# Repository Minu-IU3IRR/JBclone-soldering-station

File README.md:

# DIY Multi-Channel JBC-Compatible Soldering Station

A high-performance open hardware soldering station designed to support **JBC and other thermocouple-based soldering tips**.  
This project aims to deliver professional-grade thermal control and user experience at a fraction of the cost of a commercial JBC system.

---

## Overview

The system provides **multi-channel support**, each with independent temperature feedback loops based on PID control.  
It includes modular PCB designs, 3D-printable case that fits in a standard 200x200mm 3d printer, STM32F103 microcontroller, Nextion HMI interface

**Key features:**
- Multi-channel indipendent temperature control
- Compatible with any arbitrary tip, JBC or otherwise, as long as it uses a thermocouple
- PID temperature control with zero cross switching
- external EEprom stored calcibration and tuning  
- Nextion-based HMI for user interaction
- Fully open-source hardware and firmware

---
## Firmware Architecture

The firmware is structured into modules:

| Module | Description |
|---------|-------------|
| **Heater/** | PID controller, temperature processing, and power control routines |
| **EEprom/** | Persistent storage for calibration and configuration |
| **Hardware_definition/** | Board pin mapping, timing constants, and I/O configuration |
| **display/** | Nextion display communication handler |
| **hartbeat/** | System heartbeat and status indicator |
| **Parser/** | Command parser for serial/HMI communication |

**PID Control:**  
The controller continuously adjusts heater drive based on thermocouple feedback.  
Parameters `Kp`, `Ki`, and `Kd` can be tuned at runtime through serial commands or tuning software.

**EEPROM Configuration:**  
All configuration data (tip profiles, PID tuning, calibration) is saved in EEPROM.  
On startup, the station loads the saved configuration automatically.

---

## Hardware Assembly

1. **PCBs:**  
   Fabricate the `mainboard` and `daughterboard` Gerbers (found under `/production/`).
2. **Mechanical design:**  
   View or download the CAD model on Onshape:  
   👉 [Onshape Assembly Model](https://cad.onshape.com/documents/a679f571d3dbe280f604253c/w/8a053e0b812f1b7821749418/e/78f31934af3d4bb4e1cbee4a)
3. **Transformer:**  
   Follow winding and connection details from the `transformer/` folder or pick a closely matched one (MUST HAVE INDIPENDENT WINDINGS FOR EACH OUTPUT)

---

## 🖥️ HMI Setup

1. Open `NX3224T024_hmi.HMI` in **Nextion Editor**.
2. Connect the display to the mainboard’s UART (`Serial1`, 115200 bps).
3. Upload the `.tft` file to the screen via SD card or serial upload or upload via SD-card, check Nextion documentation
5. The interface provides:
   - Channel selection  
   - Temperature setpoint entry  
   - Live tip temperature display

---

## Software Build

1. **Install [PlatformIO](https://platformio.org/).**
2. Open `Software/JBclone Firmware/` in VS Code.
3. Connect your STM32 board using an ST-link dongle.
4. Build and upload:
   ```bash
   pio run --target upload
   ```
5. The firmware will automatically initialize EEPROM and start monitoring the heater.

---

## Calibration & Tuning

- Refer to `cal and tuning table.ods` for measured offsets and recommended PID coefficients.  
- Store calibration through serial commands or via tuning software.  
- EEPROM ensures retention between power cycles.

---

## License

**Hardware (PCBs, transformer, mechanical design):**  
Released under the [CERN-OHL-P v2 License](https://ohwr.org/project/cernohl/wikis/Documents/CERN-OHL-version-2).  
You are free to use, modify, and distribute, provided attribution to the original project is maintained.  

**Firmware and software:**  
Released under the [MIT License](https://opensource.org/licenses/MIT).  

All content is provided **as-is** without any warranty or liability.  
Please include a reference to this repository when sharing or modifying the design.

---

## Credits

Project designed and developed by Manuel Minutello.  
Hardware and firmware are open for modification and improvement by the community.

---

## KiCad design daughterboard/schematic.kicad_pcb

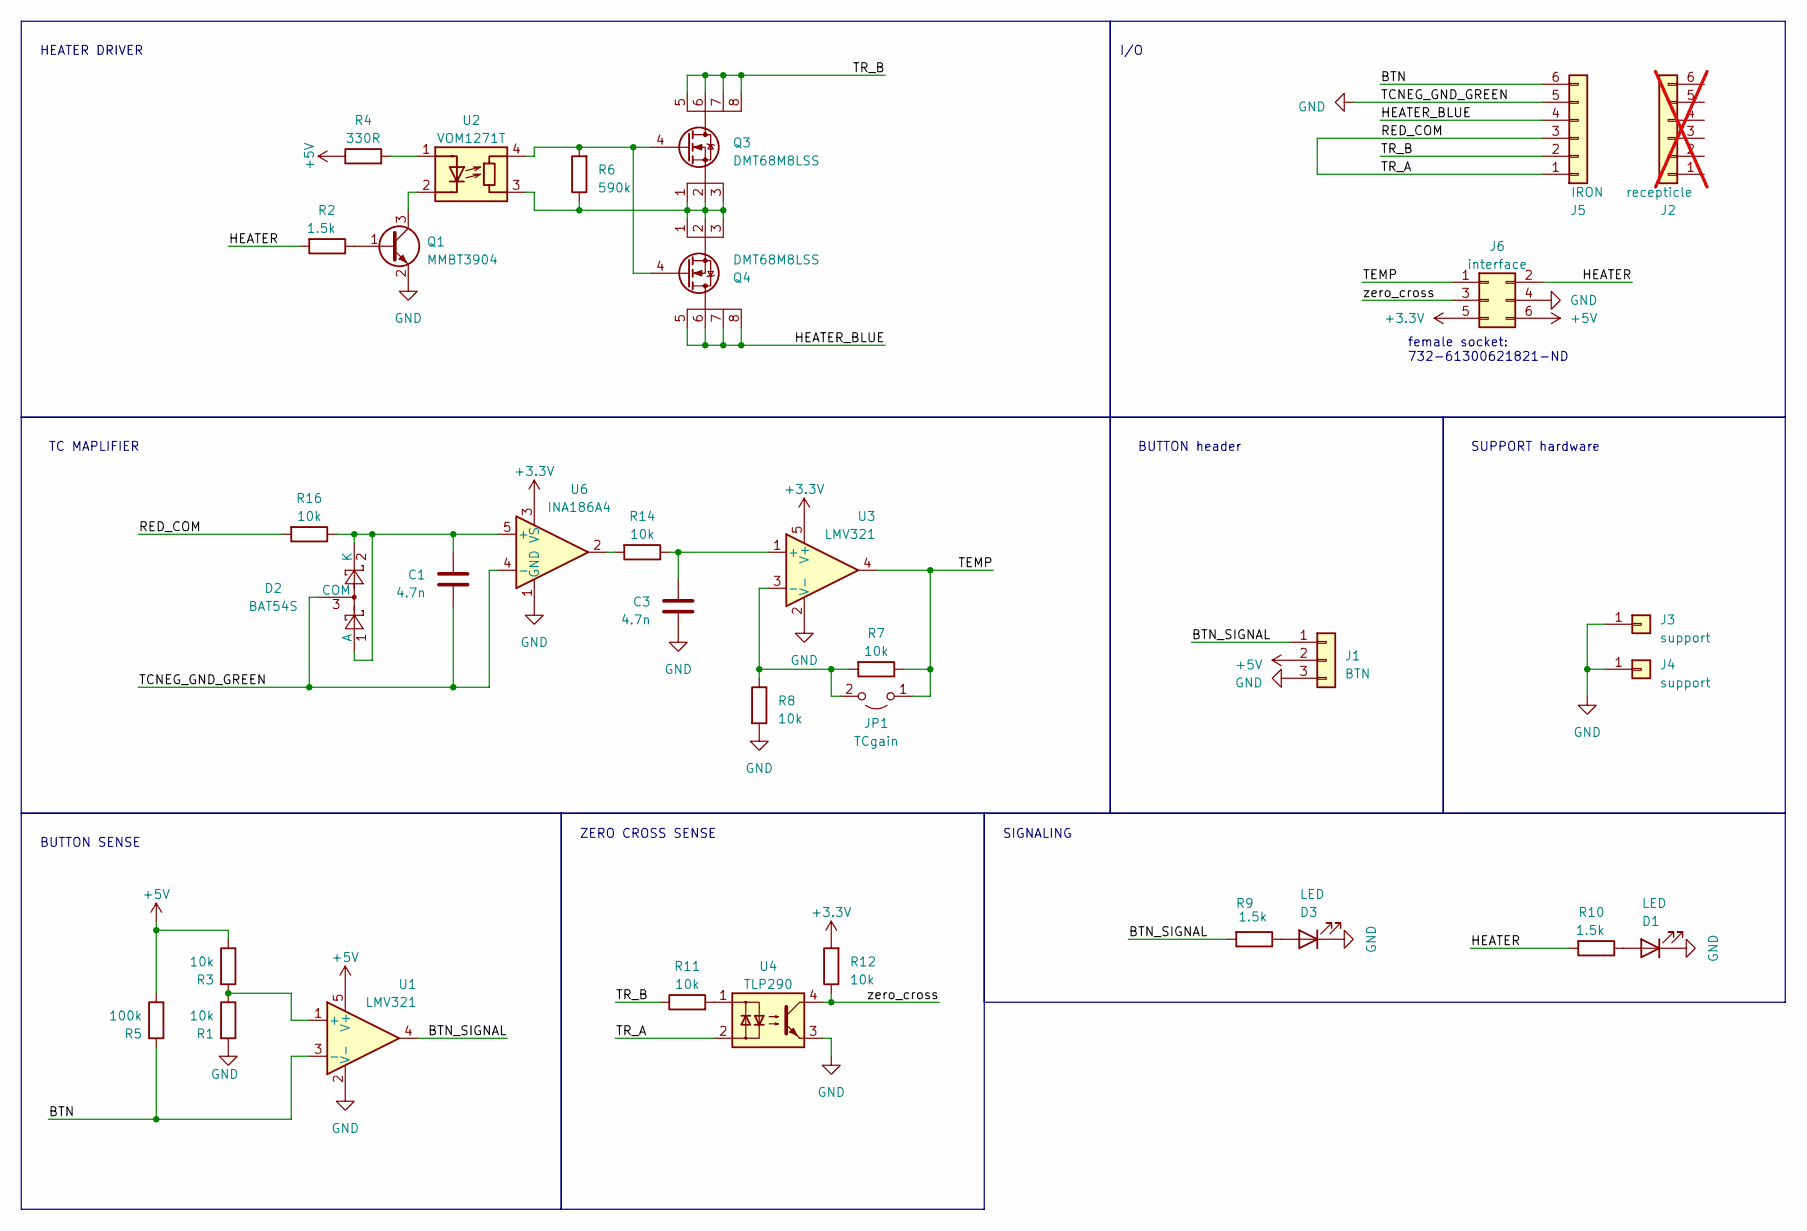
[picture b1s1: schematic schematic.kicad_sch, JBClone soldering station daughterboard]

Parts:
C1, C3: 4.7n; C_0805_2012Metric_Pad1.18x1.45mm_HandSolder; digikey 490-1634-1-ND
D1, D3: LED; LED_0805_2012Metric_Pad1.15x1.40mm_HandSolder; digikey 1516-QBLP631-IG5CT-ND
D2: BAT54S; SOT-23; digikey BAT54S-FDICT-ND
J1: BTN; PinHeader_1x03_P2.54mm_Vertical; digikey 10129378-903004BLF-ND
J2: recepticle; digikey 277-1015-ND; not fitted
J3, J4: support; AMT0440051DB; digikey 1818-AMT0440051DB0000G-ND
J5: IRON; PhoenixContact_MSTB_2,5_6-GF-5,08_1x06_P5.08mm_Horizontal_T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; digikey 277-1099-ND
J6: interface; PinHeader_2x03_P2.54mm_Horizontal; digikey 4324-PHED-RS006G1ABOGA-C006-ND
JP1: TCgain; SolderJumper-2_P1.3mm_Open_RoundedPad1.0x1.5mm; digikey NA
Q1: MMBT3904; SOT-23; digikey MMBT3904TPMSCT-ND
Q3, Q4: DMT68M8LSS; SO-8_3.9x4.9mm_P1.27mm; digikey 31-DMT68M8LSS-13CT-ND
R1, R3, R7, R8, R14, R16: 10k; R_0805_2012Metric_Pad1.20x1.40mm_HandSolder; digikey P10KACT-ND
R2, R9, R10: 1.5k; R_0805_2012Metric_Pad1.20x1.40mm_HandSolder; digikey 311-1.5KARCT-ND
R4: 330R; R_0805_2012Metric_Pad1.20x1.40mm_HandSolder; digikey P330ACT-ND
R5: 100k; R_0805_2012Metric_Pad1.20x1.40mm_HandSolder; digikey P100KACT-ND
R6: 590k; R_0805_2012Metric_Pad1.20x1.40mm_HandSolder; digikey P590KDACT-ND
R11, R12: 10k; R_0805_2012Metric; digikey P10KACT-ND
U1, U3: LMV321; SOT-23-5_HandSoldering; digikey 296-9567-1-ND
U2: VOM1271T; SOP-4; digikey VOM1271TCT-ND
U4: TLP290; SOP-4_4.4x2.6mm_P1.27mm; digikey TLP290(GB-TPSECT-ND
U6: INA186A4; SOT-23-5; digikey 296-INA186A4QDBVRQ1CT-ND

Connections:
+3.3V: J6.5, R12.2, U3.5 (V+), U6.3 (VS)
+5V: J1.2, J6.6, R3.1, R4.1, R5.1, U1.5 (V+)
/BTN: J5.6, R5.2, U1.3 (-)
/BTN_SIGNAL: J1.1, R9.2, U1.4
/HEATER: J6.2, R2.2, R10.2
/HEATER_BLUE: J5.4, Q4.5 (D), Q4.6 (D), Q4.7 (D), Q4.8 (D)
/RED_COM: J5.1, J5.3, R16.2, U4.2
/TEMP: J6.1, JP1.1 (A), R7.1, U3.4
/TR_B: J5.2, Q3.5 (D), Q3.6 (D), Q3.7 (D), Q3.8 (D), R11.1
/zero_cross: J6.3, R12.1, U4.4
GND: C1.2, C3.2, D1.1 (K), D2.3 (COM), D3.1 (K), J1.3, J3.1, J4.1, J5.5, J6.4, Q1.2 (E), R1.2, R8.2, U1.2 (V-), U3.2 (V-), U4.3, U6.1 (GND), U6.4 (-)
unnamed: D1.2 (A), R10.1
unnamed: C1.1, D2.1 (A), D2.2 (K), R16.1, U6.5 (+)
unnamed: D3.2 (A), R9.1
unnamed: JP1.2 (B), R7.2, R8.1, U3.3 (-)
unnamed: Q1.1 (B), R2.1
unnamed: Q1.3 (C), U2.2 (K)
unnamed: Q3.1 (D), Q3.2 (D), Q3.3 (G), Q4.1 (D), Q4.2 (D), Q4.3 (G), R6.1, U2.3 (R)
unnamed: Q3.4 (S), Q4.4 (S), R6.2, U2.4 (R)
unnamed: R11.2, U4.1
unnamed: R14.2, U6.2
unnamed: R1.1, R3.2, U1.1 (+)
unnamed: R4.2, U2.1 (A)
unnamed: C3.1, R14.1, U3.1 (+)

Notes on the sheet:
HEATER DRIVER
SIGNALING
female socket: 732-61300621821-ND
I/O
SUPPORT hardware
TC MAPLIFIER
BUTTON SENSE
ZERO CROSS SENSE
BUTTON header

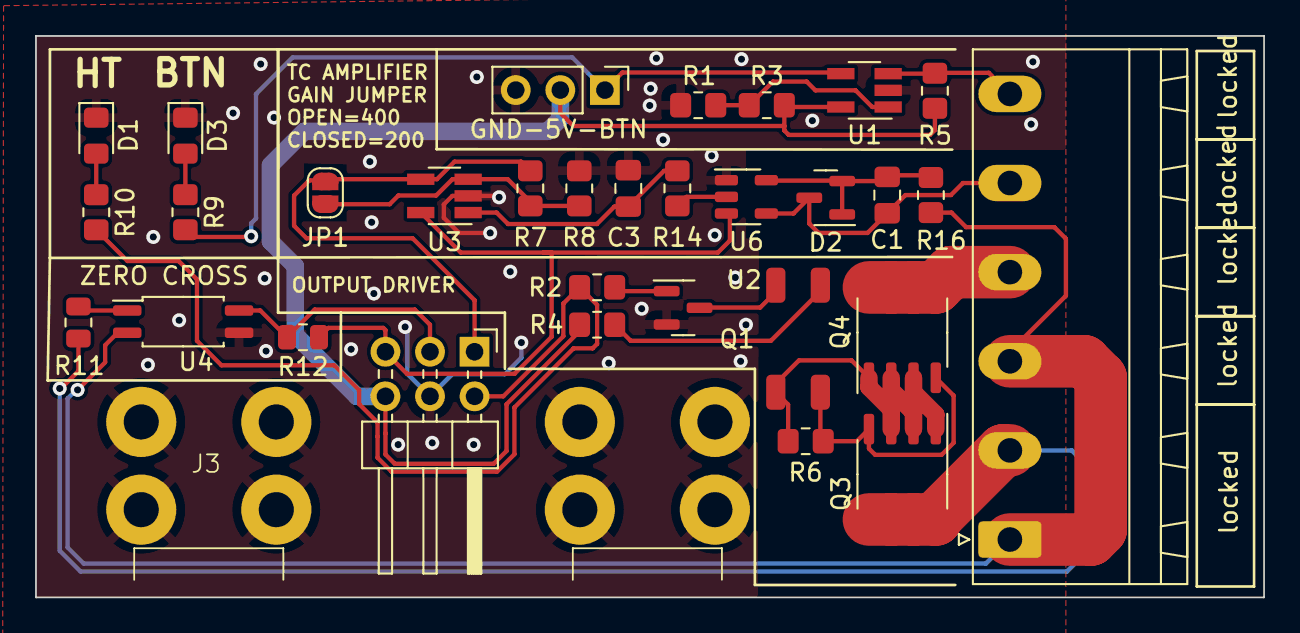
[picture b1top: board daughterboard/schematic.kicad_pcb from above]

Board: 2 copper layers, 70.0 x 32.0 mm, 33 parts (0 on the bottom side), 24 nets.

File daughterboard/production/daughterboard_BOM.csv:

"Reference","Value","Footprint","Datasheet","digikey","Qty"
"C1, C3","4.7n","Capacitor_SMD:C_0805_2012Metric_Pad1.18x1.45mm_HandSolder","https://search.murata.co.jp/Ceramy/image/img/A01X/G101/ENG/G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","490-1634-1-ND","2"
"D1, D3","LED","LED_SMD:LED_0805_2012Metric_Pad1.15x1.40mm_HandSolder","https://www.qt-brightek.com/datasheet/QBLP631-IG5.pdf","1516-QBLP631-IG5CT-ND","2"
"D2","BAT54S","Package_TO_SOT_SMD:SOT-23","https://www.diodes.com/assets/Datasheets/BAT54_A_C_S.pdf","BAT54S-FDICT-ND","1"
"J1","BTN","Connector_PinHeader_2.54mm:PinHeader_1x03_P2.54mm_Vertical","https://cdn.amphenol-cs.com/media/wysiwyg/files/documentatio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","10129378-903004BLF-ND","1"
"J2","recepticle","","https://www.phoenixcontact.com/en-us/products/pcb-plug-mstb-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","277-1015-ND","1"
"J3, J4","support","01_custom footprint:AMT0440051DB","https://www.anytek.com.cn/Upload/AMT0440051DB0000G-67c577521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","1818-AMT0440051DB0000G-ND","2"
"J5","IRON","Connector_Phoenix_MSTB:PhoenixContact_MSTB_2,5_6-GF-5,08_1x06_P5.08mm_Horizontal_ThreadedFlange","https://www.phoenixcontact.com/us/products/1759059/pdf","277-1099-ND","1"
"J6","interface","Connector_PinHeader_2.54mm:PinHeader_2x03_P2.54mm_Horizontal","https://mm.digikey.com/Volume0/opasdata/d220001/medias/docus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","4324-PHED-RS006G1ABOGA-C006-ND","1"
"JP1","TCgain","Jumper:SolderJumper-2_P1.3mm_Open_RoundedPad1.0x1.5mm","NA","NA","1"
"Q1","MMBT3904","Package_TO_SOT_SMD:SOT-23","https://www.mccsemi.com/pdf/Products/MMBT3904(SOT-23).pdf","MMBT3904TPMSCT-ND","1"
"Q3, Q4","DMT68M8LSS","Package_SO:SO-8_3.9x4.9mm_P1.27mm","https://www.diodes.com/assets/Datasheets/DMT68M8LSS.pdf","31-DMT68M8LSS-13CT-ND","2"
"R1, R3, R7, R8, R14, R16","10k","Resistor_SMD:R_0805_2012Metric_Pad1.20x1.40mm_HandSolder","https://industrial.panasonic.com/ww/products/pt/general-purp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","P10KACT-ND","6"
"R2, R9, R10","1.5k","Resistor_SMD:R_0805_2012Metric_Pad1.20x1.40mm_HandSolder","https://www.yageo.com/upload/media/product/products/datashee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","311-1.5KARCT-ND","3"
"R4","330R","Resistor_SMD:R_0805_2012Metric_Pad1.20x1.40mm_HandSolder","https://industrial.panasonic.com/ww/products/pt/general-purp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","P330ACT-ND","1"
"R5","100k","Resistor_SMD:R_0805_2012Metric_Pad1.20x1.40mm_HandSolder","https://industrial.panasonic.com/ww/products/pt/general-purp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","P100KACT-ND","1"
"R6","590k","Resistor_SMD:R_0805_2012Metric_Pad1.20x1.40mm_HandSolder","https://industrial.panasonic.com/cdbs/www-data/pdf/RDM0000/A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","P590KDACT-ND","1"
"R11, R12","10k","Resistor_SMD:R_0805_2012Metric","https://industrial.panasonic.com/ww/products/pt/general-purp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","P10KACT-ND","2"
"U1, U3","LMV321","Package_TO_SOT_SMD:SOT-23-5_HandSoldering","https://rocelec.widen.net/view/pdf/hsbslfymvc/slos263w.pdf?t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","296-9567-1-ND","2"
"U2","VOM1271T","01_custom footprint:SOP-4","https://www.vishay.com/docs/83469/vom1271.pdf","VOM1271TCT-ND","1"
"U4","TLP290","Package_SO:SOP-4_4.4x2.6mm_P1.27mm","https://toshiba.semicon-storage.com/info/docget.jsp?did=1288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","TLP290(GB-TPSECT-ND","1"
"U6","INA186A4","Package_TO_SOT_SMD:SOT-23-5","https://www.ti.com/lit/ds/symlink/ina186-q1.pdf","296-INA186A4QDBVRQ1CT-ND","1"

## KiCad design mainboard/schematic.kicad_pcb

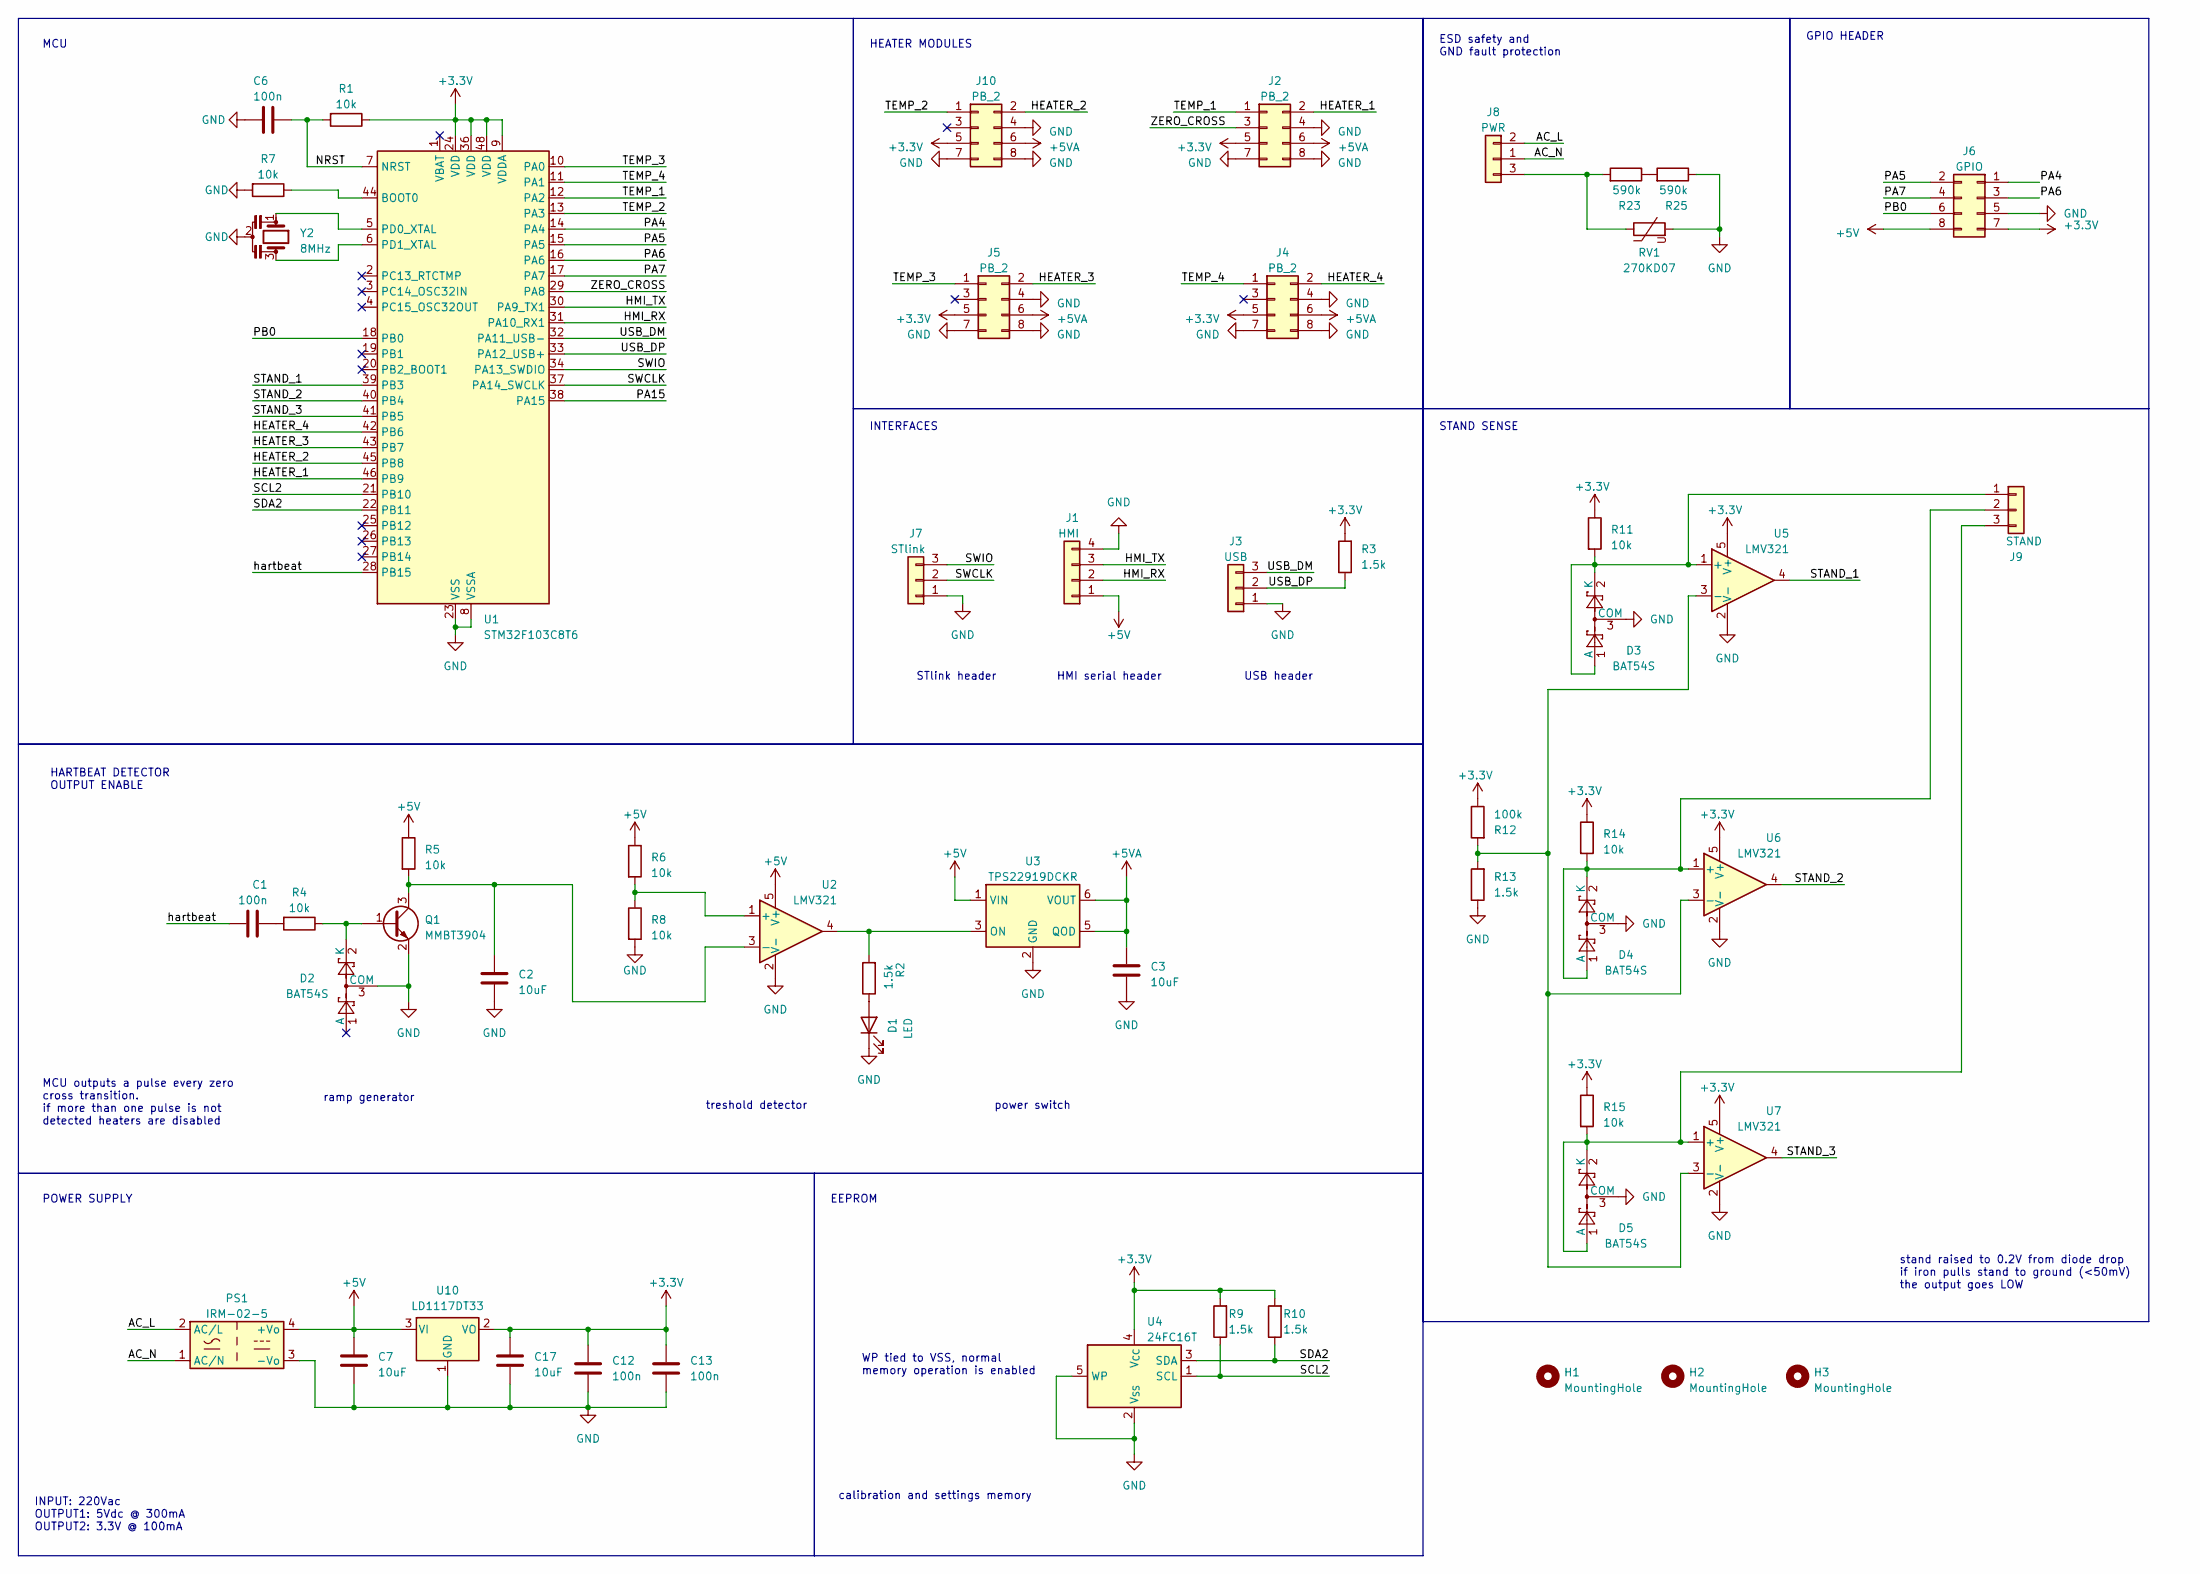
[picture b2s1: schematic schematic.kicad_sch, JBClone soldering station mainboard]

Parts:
C1, C6, C12, C13: 100n; C_0805_2012Metric_Pad1.18x1.45mm_HandSolder; digikey 1276-1003-1-ND
C2, C3, C7, C17: 10uF; C_0805_2012Metric_Pad1.18x1.45mm_HandSolder; digikey 1276-1096-1-ND
D1: LED; LED_0805_2012Metric_Pad1.15x1.40mm_HandSolder; digikey 1516-QBLP631-IG5CT-ND
D2, D3, D4, D5: BAT54S; SOT-23; digikey BAT54S-FDICT-ND
H1, H2, H3: MountingHole; MountingHole_3.2mm_M3; digikey N/A
J1: HMI; PinHeader_1x04_P2.54mm_Vertical; digikey 664-G800W304018EU-ND
J2, J4, J5, J10: PB_2; DaughterBoard; digikey 732-61300621821-ND
J3: USB; PinHeader_1x03_P2.54mm_Vertical; digikey 664-G800W305018EU-ND
J6: GPIO; PinSocket_2x04_P2.54mm_Vertical; digikey 732-61300621821-ND
J7: STlink; PinHeader_1x03_P2.54mm_Vertical; digikey 664-G800W305018EU-ND
J8: PWR; TerminalBlock_Phoenix_MKDS-1,5-3-5.08_1x03_P5.08mm_Horizont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; digikey 277-1264-ND
J9: STAND; PinHeader_1x03_P2.54mm_Vertical; digikey 664-G800W305018EU-ND
PS1: IRM-02-5; Converter_ACDC_MeanWell_IRM-02-xx_THT; digikey 1866-3009-ND
Q1: MMBT3904; SOT-23; digikey MMBT3904TPMSCT-ND
R1, R4, R5, R6, R7, R8, R11, R14, R15: 10k; R_0805_2012Metric_Pad1.20x1.40mm_HandSolder; digikey P10KACT-ND
R2, R3, R9, R10, R13: 1.5k; R_0805_2012Metric_Pad1.20x1.40mm_HandSolder; digikey 311-1.5KARCT-ND
R12: 100k; R_0805_2012Metric_Pad1.20x1.40mm_HandSolder; digikey P100KACT-ND
R23, R25: 590k; R_0805_2012Metric_Pad1.20x1.40mm_HandSolder; digikey P590KDACT-ND
RV1: 270KD07; RV_Disc_D7mm_W4.8mm_P5mm; digikey 13-270KD07-ND
U1: STM32F103C8T6; LQFP-48_7x7mm_P0.5mm; digikey 497-17666-1-ND
U2, U5, U6, U7: LMV321; SOT-23-5_HandSoldering; digikey 296-9567-1-ND
U3: TPS22919DCKR; SOT-23-6_Handsoldering; digikey 296-TPS22919DCKRCT-ND
U4: 24FC16T; SOT-23-5_HandSoldering; digikey 150-24FC16T-I/OTCT-ND
U10: LD1117DT33; TO-252-2; digikey 497-1235-1-ND
Y2: 8MHz; Resonator_SMD_Murata_CSTxExxV-3Pin_3.0x1.1mm_HandSoldering; digikey 490-17958-1-ND

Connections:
+3.3V: C12.1, C13.1, C17.1, J2.5, J4.5, J5.5, J6.7, J10.5, R1.1, R3.2, R9.2, R10.2, R11.1, R12.1, R14.1, R15.1, U1.9 (VDDA), U1.24 (VDD), U1.36 (VDD), U1.48 (VDD), U4.4 (V_{CC}), U5.5 (V+), U6.5 (V+), U7.5 (V+), U10.2 (VO)
+5V: C7.1, J1.1, J6.8, PS1.4 (+Vo), R5.1, R6.1, U2.5 (V+), U3.1 (VIN), U10.3 (VI)
+5VA: C3.1, J2.6, J4.6, J5.6, J10.6, U3.5 (QOD), U3.6 (VOUT)
/AC_L: J8.2 (Pin_1), PS1.2 (AC/L)
/AC_N: J8.1 (Pin_2), PS1.1 (AC/N)
/HEATER_1: J2.2, U1.46 (PB9)
/HEATER_2: J10.2, U1.45 (PB8)
/HEATER_3: J5.2, U1.43 (PB7)
/HEATER_4: J4.2, U1.42 (PB6)
/HMI_RX: J1.2, U1.31 (PA10_RX1)
/HMI_TX: J1.3, U1.30 (PA9_TX1)
/NRST: C6.1, R1.2, U1.7 (NRST)
/PA4: J6.1, U1.14 (PA4)
/PA5: J6.2, U1.15 (PA5)
/PA6: J6.3, U1.16 (PA6)
/PA7: J6.4, U1.17 (PA7)
/PA15: U1.38 (PA15)
/PB0: J6.6, U1.18 (PB0)
/SCL2: R9.1, U1.21 (PB10), U4.1 (SCL)
/SDA2: R10.1, U1.22 (PB11), U4.3 (SDA)
/STAND_1: U1.39 (PB3), U5.4
/STAND_2: U1.40 (PB4), U6.4
/STAND_3: U1.41 (PB5), U7.4
/SWCLK: J7.2, U1.37 (PA14_SWCLK)
/SWIO: J7.3, U1.34 (PA13_SWDIO)
/TEMP_1: J2.1, U1.12 (PA2)
/TEMP_2: J10.1, U1.13 (PA3)
/TEMP_3: J5.1, U1.10 (PA0)
/TEMP_4: J4.1, U1.11 (PA1)
/USB_DM: J3.3, U1.32 (PA11_USB-)
/USB_DP: J3.2, R3.1, U1.33 (PA12_USB+)
/ZERO_CROSS: J2.3, U1.29 (PA8)
/hartbeat: C1.1, U1.28 (PB15)
GND: C2.2, C3.2, C6.2, C7.2, C12.2, C13.2, C17.2, D1.1 (K), D2.3 (COM), D3.3 (COM), D4.3 (COM), D5.3 (COM), J1.4, J2.4, J2.7, J2.8, J3.1, J4.4, J4.7, J4.8, J5.4, J5.7, J5.8, J6.5, J7.1, J10.4, J10.7, J10.8, PS1.3 (-Vo), Q1.2 (E), R7.2, R8.2, R13.1, R25.1, RV1.2, U1.8 (VSSA), U1.23 (VSS), U1.35 (VSS), U1.47 (VSS), U2.2 (V-), U3.2 (GND), U4.2 (V_{SS}), U4.5 (WP), U5.2 (V-), U6.2 (V-), U7.2 (V-), U10.1 (GND), Y2.2
unnamed: C1.2, R4.2
unnamed: D1.2 (A), R2.1
unnamed: D2.2 (K), Q1.1 (B), R4.1
unnamed: D3.1 (A), D3.2 (K), J9.1, R11.2, U5.1 (+)
unnamed: D4.1 (A), D4.2 (K), J9.2, R14.2, U6.1 (+)
unnamed: D5.1 (A), D5.2 (K), J9.3, R15.2, U7.1 (+)
unnamed: J8.3, R23.2, RV1.1
unnamed: C2.1, Q1.3 (C), R5.2, U2.3 (-)
unnamed: R23.1, R25.2
unnamed: R7.1, U1.44 (BOOT0)
unnamed: U1.5 (PD0_XTAL), Y2.1
unnamed: U1.6 (PD1_XTAL), Y2.3
unnamed: R6.2, R8.1, U2.1 (+)
unnamed: R2.2, U2.4, U3.3 (ON)
unnamed: R12.2, R13.2, U5.3 (-), U6.3 (-), U7.3 (-)

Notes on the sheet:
STlink header
POWER SUPPLY
ESD safety and GND fault protection
HARTBEAT DETECTOR OUTPUT ENABLE
INTERFACES
ramp generator
USB header
HMI serial header
WP tied to VSS, normal memory operation is enabled
calibration and settings memory
INPUT: 220Vac OUTPUT1: 5Vdc @ 300mA OUTPUT2: 3.3V @ 100mA
GPIO HEADER
MCU outputs a pulse every zero cross transition. if more than one pulse is not detected heaters are disabled
EEPROM
STAND SENSE
stand raised to 0.2V from diode drop if iron pulls stand to ground (<50mV) the output goes LOW
treshold detector
power switch
MCU
HEATER MODULES

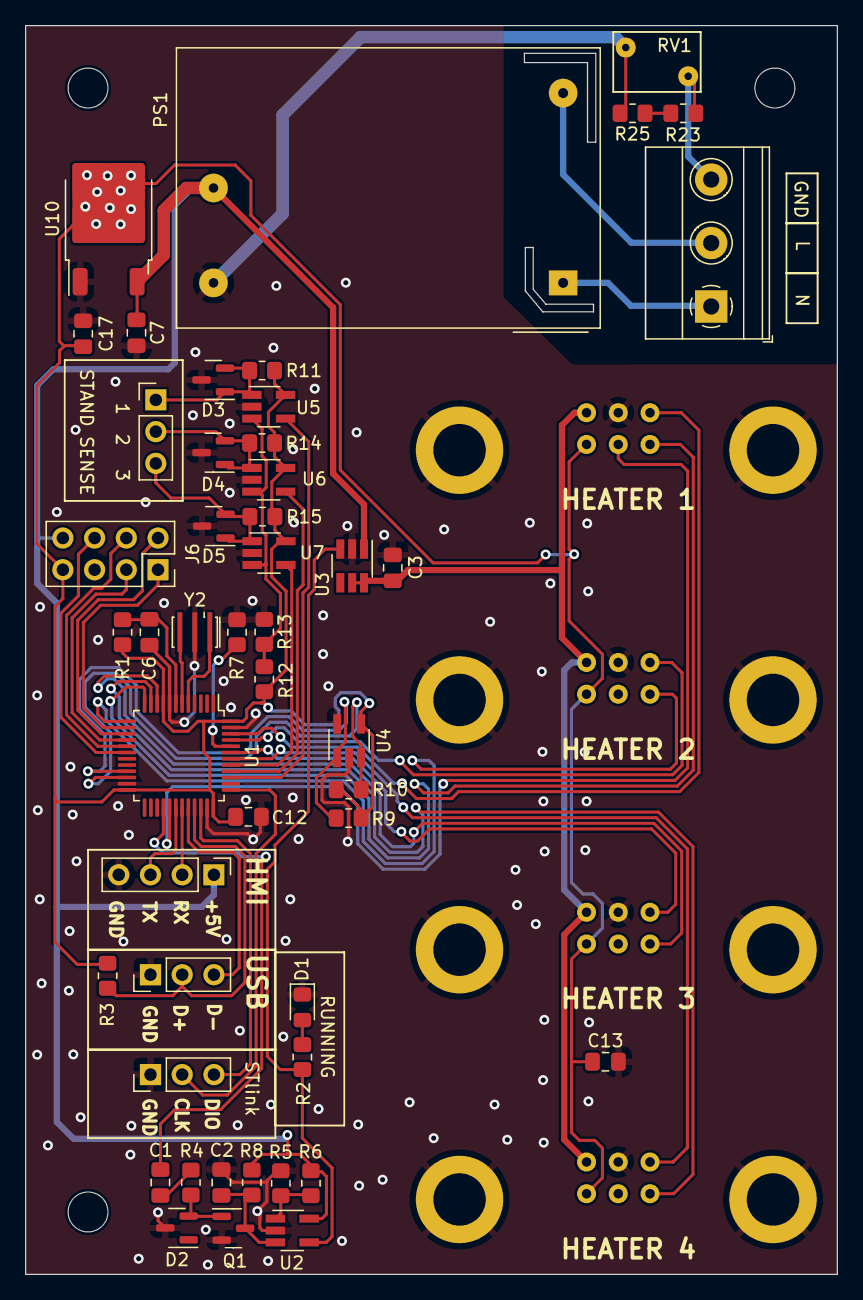
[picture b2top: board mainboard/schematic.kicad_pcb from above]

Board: 2 copper layers, 65.0 x 100.0 mm, 55 parts (0 on the bottom side), 48 nets.

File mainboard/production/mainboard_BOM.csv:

"Reference","Value","Footprint","Datasheet","digikey","Qty"
"C1, C6, C12, C13","100n","Capacitor_SMD:C_0805_2012Metric_Pad1.18x1.45mm_HandSolder","https://mm.digikey.com/Volume0/opasdata/d220001/medias/docus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","1276-1003-1-ND","4"
"C2, C3, C7, C17","10uF","Capacitor_SMD:C_0805_2012Metric_Pad1.18x1.45mm_HandSolder","https://mm.digikey.com/Volume0/opasdata/d220001/medias/docus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","1276-1096-1-ND","4"
"D1","LED","LED_SMD:LED_0805_2012Metric_Pad1.15x1.40mm_HandSolder","https://www.qt-brightek.com/datasheet/QBLP631-IG5.pdf","1516-QBLP631-IG5CT-ND","1"
"D2-D5","BAT54S","Package_TO_SOT_SMD:SOT-23","https://www.diodes.com/assets/Datasheets/BAT54_A_C_S.pdf","BAT54S-FDICT-ND","4"
"H1-H3","MountingHole","MountingHole:MountingHole_3.2mm_M3","N/A","N/A","3"
"J1","HMI","Connector_PinHeader_2.54mm:PinHeader_1x04_P2.54mm_Vertical","https://cdn.amphenol-cs.com/media/wysiwyg/files/drawing/g800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","664-G800W304018EU-ND","1"
"J2, J4, J5, J10","PB_2","01_ProjectFootprint:DaughterBoard","https://www.we-online.com/components/products/datasheet/6130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","732-61300621821-ND","4"
"J3","USB","Connector_PinHeader_2.54mm:PinHeader_1x03_P2.54mm_Vertical","https://cdn.amphenol-cs.com/media/wysiwyg/files/drawing/g800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","664-G800W305018EU-ND","1"
"J6","GPIO","Connector_PinSocket_2.54mm:PinSocket_2x04_P2.54mm_Vertical","https://www.we-online.com/components/products/datasheet/6130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","732-61300621821-ND","1"
"J7","STlink","Connector_PinHeader_2.54mm:PinHeader_1x03_P2.54mm_Vertical","https://cdn.amphenol-cs.com/media/wysiwyg/files/drawing/g800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","664-G800W305018EU-ND","1"
"J8","PWR","TerminalBlock_Phoenix:TerminalBlock_Phoenix_MKDS-1,5-3-5.08_1x03_P5.08mm_Horizontal","https://www.phoenixcontact.com/us/products/1715734/pdf","277-1264-ND","1"
"J9","STAND","Connector_PinHeader_2.54mm:PinHeader_1x03_P2.54mm_Vertical","https://cdn.amphenol-cs.com/media/wysiwyg/files/drawing/g800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","664-G800W305018EU-ND","1"
"PS1","IRM-02-5","Converter_ACDC:Converter_ACDC_MeanWell_IRM-02-xx_THT","https://www.meanwell.com/Upload/PDF/IRM-02/IRM-02-SPEC.PDF","1866-3009-ND","1"
"Q1","MMBT3904","Package_TO_SOT_SMD:SOT-23","https://www.mccsemi.com/pdf/Products/MMBT3904(SOT-23).pdf","MMBT3904TPMSCT-ND","1"
"R1, R4-R8, R11, R14, R15","10k","Resistor_SMD:R_0805_2012Metric_Pad1.20x1.40mm_HandSolder","https://industrial.panasonic.com/ww/products/pt/general-purp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","P10KACT-ND","9"
"R2, R3, R9, R10, R13","1.5k","Resistor_SMD:R_0805_2012Metric_Pad1.20x1.40mm_HandSolder","https://www.yageo.com/upload/media/product/products/datashee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","311-1.5KARCT-ND","5"
"R12","100k","Resistor_SMD:R_0805_2012Metric_Pad1.20x1.40mm_HandSolder","https://industrial.panasonic.com/ww/products/pt/general-purp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","P100KACT-ND","1"
"R23, R25","590k","Resistor_SMD:R_0805_2012Metric_Pad1.20x1.40mm_HandSolder","https://industrial.panasonic.com/cdbs/www-data/pdf/RDM0000/A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","P590KDACT-ND","2"
"RV1","270KD07","Varistor:RV_Disc_D7mm_W4.8mm_P5mm","https://www.yageo.com/upload/media/product/app/datasheet/cpc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","13-270KD07-ND","1"
"U1","STM32F103C8T6","Package_QFP:LQFP-48_7x7mm_P0.5mm","https://www.st.com/resource/en/datasheet/stm32f103cb.pdf","497-17666-1-ND","1"
"U2, U5-U7","LMV321","Package_TO_SOT_SMD:SOT-23-5_HandSoldering","https://rocelec.widen.net/view/pdf/hsbslfymvc/slos263w.pdf?t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","296-9567-1-ND","4"
"U3","TPS22919DCKR","Package_TO_SOT_SMD:SOT-23-6_Handsoldering","https://www.ti.com/lit/ds/symlink/tps22919.pdf","296-TPS22919DCKRCT-ND","1"
"U4","24FC04HT","Package_TO_SOT_SMD:SOT-23-5_HandSoldering","https://ww1.microchip.com/downloads/en/DeviceDoc/24AA04H-24L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","24FC04HT-I/OTCT-ND","1"
"U10","LD1117DT33","Package_TO_SOT_SMD:TO-252-2","https://www.st.com/content/ccc/resource/technical/document/d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","497-1235-1-ND","1"
"Y2","8MHz","Crystal:Resonator_SMD_Murata_CSTxExxV-3Pin_3.0x1.1mm_HandSoldering","https://www.murata.com/en/products/productdata/8801161740318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","490-17958-1-ND","1"

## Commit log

2025-11-04 Update README with project details and features
    Added detailed project description and features to README.
2026-01-09 added PDF print of schematic
2026-01-09 added PDF of schematic
